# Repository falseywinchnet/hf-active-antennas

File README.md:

For the glory and the service of our God.

# HF active antennas

These are three open-hardware HF receive-antenna amplifiers. Each one ships with:
- an LTspice model you can simulate as delivered;
- a KiCad 10 board;
- JLCPCB-ready gerbers, BOM and pick-and-place;
- 3D renders and simulation plots.

All three use the Linear Systems **LSBF862** ultra-low-noise JFET at the input.

| | | |
|:---:|:---:|:---:|
|  |  |  |
| **[WB-2: zero-flux loop amplifier](wb2-loop-amplifier/)** | **[WB-LNA: loop preamplifier](wb-lna-loop-preamp/)** | **[MW-1: mini-whip E-field probe](mw1-mini-whip/)** |
| A balanced, transformer-feedback (zero-flux) amplifier for small receiving loops, Wellbrook ALA1530 class. 8 + 8 LSBF862, catalog Coilcraft transformers, 75 Ω F out. | A single-ended high-impedance preamp for a loop or any high-Z HF source. 4× LSBF862 common source → 4× NSVF4009 with shunt feedback, 50 Ω SMA. | A charge amplifier for a small capacitive plate (PA0RDT / PA3FWM class), built for linearity and spike survival. Jumper gain steps, 75 Ω F out, phantom power. |
| 0.1–30 MHz · 21.6 dB · NF 0.2–1.3 dB (50 Ω source) | 0.03–30 MHz · 24 dB · NF 0.8–1.1 dB | 9 kHz–30 MHz · OIP3 +47 dBm · OIP2 +73 dBm |
|  |  |  |

*Top row: KiCad 3D renders of the actual boards. Bottom row: AI-generated concept renders of the intended builds (ChatGPT image generation, from the KiCad renders and enclosure dimensions). They are not photographs; nothing has been built yet.*

## What is in each folder

| path | contents |
|---|---|
| `README.md` | the explanation, performance tables, plots and ordering notes |
| `images/` | 3D renders, copper plots, and the schematic as PNG and SVG |
| `ltspice/` | the `.asc` schematic plus every model library it needs. Open the `.asc` in LTspice and press Run; the `.lib` paths are relative. |
| `plots/` | simulation results |
| `jlcpcb/` | `*_gerbers_drill.zip` (upload this), the unzipped gerbers and drill files, `BOM_JLCPCB.csv` and `CPL_JLCPCB.csv` |
| `BOM.csv` | the full bill of materials, with manufacturer, MPN, footprint and status |
| `kicad/` | KiCad 10 board, project, custom footprint libraries and the DRC report |
| `*.step` | 3D board model for enclosure work |

## Status: read this before ordering
- **Simulation only.** Every performance figure here comes from LTspice. That includes nominal and tolerance corners, layout-parasitic models of the boards, and stability margins. **None of these boards has been built or measured yet.**
  - Treat the first boards as prototypes.
  - WB-2 has a first-board bring-up procedure in [`wb2-loop-amplifier/docs/BRINGUP.md`](wb2-loop-amplifier/docs/BRINGUP.md).
- **The LSBF862 is not stocked at LCSC.** Buy it from Linear Integrated Systems or a distributor, then hand-fit it or consign it to JLCPCB. The same applies to the Coilcraft transformers on WB-2.
- **No surge, ESD or lightning rating is claimed.** All three boards have protection networks, but none has been tested.
- **Check rotations in JLCPCB's placement preview.** KiCad and JLC disagree on the zero orientation of several packages (SOT-23, SOD-323, SC-82FL and others).
- **Model provenance:**
  - The LSBF862, NSVF4009 and MMBTH81 models are transcriptions of the manufacturers' published SPICE parameters, with LTspice syntax fixes noted in each file header.
  - The BC817-25 and 1N5819 come from LTspice's standard library.
  - The NSVF4015 model is a fit to its datasheet; onsemi publishes no model for it.
  - The protection parts, op-amps and the eFuse are behavioural.

## Tools
- [`tools/asc_render.py`](tools/asc_render.py) renders an LTspice `.asc` to PNG/SVG using LTspice's own symbol graphics. It needs LTspice installed for the `.asy` files. The schematic images were made with it.
- [`tools/net_compare.py`](tools/net_compare.py) compares an LTspice-generated `.net` against a reference SPICE netlist: element by element, value by value, with topology up to net renaming.
  - The WB-2 schematic is generated from the design's netlist and checked with it: 240 elements, 0 differences.
  - The AC response is identical to 1e-10 dB.

## License
Hardware design files, models and documentation are released under the **CERN Open Hardware Licence Version 2 – Permissive** ([`LICENSE`](LICENSE), SPDX `CERN-OHL-P-2.0`). They are provided as-is, without warranty; see sections 6–7 of the licence.

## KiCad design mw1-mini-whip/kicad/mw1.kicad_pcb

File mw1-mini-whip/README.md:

# MW-1: mini-whip E-field probe amplifier

*Concept render: AI-generated (ChatGPT image generation) from the KiCad renders and the enclosure dimensions, with a ruler for scale. It shows the intended build; it is **not** a photograph of a built unit.*

MW-1 is an active receiving antenna for 9 kHz – 30 MHz in the PA0RDT / PA3FWM / GigActiv class: a small capacitive plate on a mast, read by a low-noise amplifier.
- **Circuit:** a **charge amplifier** rather than the usual source follower. Gain is set by capacitance alone, so the gain steps are noiseless.
- **Design priorities:** linearity, overload margin and survival of nearby static and lightning spikes.
- **Plate:** 3 × 2 in (or a wire of similar size), about 10 pF.
- **Output and power:** 75 Ω F jack; +12 V phantom power up the coax.

## Performance
Simulated, coax-fed from a 12 V bias-T, so VCC at the board is 10.98 V at 103 mA. Field figures are referred to h_eff = 1 m.

| | 9 kHz | 100 kHz | 1 MHz | 7 MHz | 10 MHz | 30 MHz |
|---|---|---|---|---|---|---|
| Gain (V into 50 Ω per V/m) | −6.4 dB | −3.9 dB | −3.9 dB | −3.8 dB | −3.8 dB | −5.3 dB |
| Field noise (nV/m/√Hz) | | 30.5 | 4.5 | 3.4 | 3.4 | 3.8 |

- **OIP3** (7.0 / 7.1 MHz): **+47.3 dBm** at −3 dBm/tone; +44.3 dBm at +9 dBm/tone.
- **OIP2:** **+73.4 dBm**.
- **Output P1dB:** about +20 dBm.
- **FM band** (88–108 MHz): about −18 to −23 dB relative to 1 MHz.
- **Mains:** 50/60 Hz is about −110 dB.

**Installed height.** On a 3–4 m mast, h_eff is expected to be about 3.5 m. That lowers the field-referred noise about 3.5× (−11 dB), to roughly 1 nV/m/√Hz. That is 10–20 dB under quiet-rural plus galactic noise, so **overload margin, not sensitivity, is what the design spends its effort on.**

**Gain steps** (fit **at most one** jumper; output knee at h_eff 3.5 m, noise at 10 MHz with h_eff 1 m):

| jumper | added C_f | gain | output knee | noise floor |
|---|---|---|---|---|
| none | – | −3.9 dB | 1.5 V/m pk | 3.4 nV/m |
| JP1 | 33 pF | −13.6 dB | 4.5 V/m | 5.0 nV/m |
| JP2 | 130 pF | −23.6 dB | 14 V/m | 10.8 nV/m |
| JP3 | 470 pF | −33.5 dB | 44 V/m | 29 nV/m |

**Against published designs** (theirs measured or from datasheets, ours simulated):

| | OIP3 | OIP2 | field noise |
|---|---|---|---|
| **MW-1** | +47 dBm | +73 dBm | 3.4 nV/m/√Hz at h_eff 1 m |
| PA3FWM improved mini-whip | +40 to +43 | ≈ +70 | – |
| PA0RDT mini-whip | > +30 | > +50 | – |
| NTi GigActiv GA3005 | > +30 | > +50 | not published |
| R&S HE016 (6 m mast) | ≥ +30 | ≥ +50 | < 3.16 nV/m/√Hz |

## How it works

**Capacitive matching sets the floor.** The plate is a voltage source (E · h_eff) behind its own capacitance C_s. The field-referred noise floor is en · (C_s + C_stray + C_device) / (C_s · h_eff).
- **Every capacitance on the gate node counts.** That includes bootstrapped capacitance: a bootstrap's drive carries the device's own noise back through the same capacitor. This is Radeka's result for charge preamplifiers. It is why bootstrapping, the usual mini-whip trick, buys linearity but not noise.
- **Device choice:** with a 10 pF plate, the optimum device has C_dev ≈ C_s + stray. That points to the LSBF862.

**A charge amplifier instead of a follower:**
- **Input:** 2× LSBF862 in common source with an LSBF862 cascode, into an MMBTH81 current-source load.
- **Gain and output:** an NSVF4015 Darlington into two emitter followers, with NSVF4015 current sinks. The whole output stage is inside the loop.
- **Feedback:** C_f = 15 pF from OUT back to the gate, so the gate sits at virtual ground.
  - The JFET junctions barely move, which is where the +47 dBm OIP3 comes from.
  - Gain is C_s / C_f.
  - Raising C_f with a jumper raises headroom faster than it raises the noise floor. The steps are switched capacitance, so they add no noise.
- **Low-frequency and DC control:**
  - 1.5 MΩ + 100 nF in parallel with C_f roll off the low end and reject mains.
  - A BAV99 limiter in the feedback stops hard overload from latching the loop.
  - A TL431 / LM2904 bias and DC servo hold OUT at about 0.47 × VCC.

**Spike survival:** the protection is a staged chain.
- **Chain:**
  - a 90 V GDT and an SP4022 TVS at the plate;
  - a ±1.2 V BAV99 plate clamp, returned to its own decoupled node;
  - 100 Ω;
  - a ±0.6 V gate clamp.
- **Simulated with 20 V to 5 kV spikes** (ns edges) at the plate:
  - the output is pinned for ≤ 0.12 µs;
  - the in-band output is back under 10 mV in about 55 µs;
  - JFET gate conduction is ≤ 4.3 mA for about 1 ns.

**Power:** +12 V phantom only, through FB1 (600 Ω bead), then a 1 mH Würth WE-LQS choke, then 1 µF and an SMBJ15A, then a 100 µH / 47 µF filter, then 2.2 Ω, then VCC.
- **Feed drop:** about 1 V. A 13.8 V feed restores full headroom.
- **Bias-T:** not supplied. Use one rated ≥ 12 V / 150 mA with ≥ 1 kΩ choke impedance from 9 kHz to 30 MHz.

**Installation matters as much as the circuit.** The coax shield and mast are part of the antenna (PA3FWM). Ground the mast at its base and fit a common-mode choke on the coax there; Claessens measured a 15 dB difference.

## Plots

These curves come from the shipped `ltspice/mw1.asc`, not the design's Python reference model. The two agree within 0.5 dB.
- **Gain at 30 MHz:** −4.9 dB from the schematic, against the −5.3 dB in the table, which includes the layout estimate.
- **Field noise:** 4.5 / 3.3 / 3.4 / 3.7 nV/m at 1 / 7 / 10 / 30 MHz.

## LTspice model

`ltspice/mw1.asc` is the hand-laid schematic. Keep `lsbf862-ltspice.lib`, `mw-parts.lib`, `lna-parts.lib` and `mw1-nodeset.inc` next to it.
- **Test fixture:** VOC (AC 1 = 1 V/m at h_eff 1 m) behind the 10 pF plate capacitance, a 12 V shack bias-T, and a 50 Ω receiver. `V(rlo)` is the output.
- **Gain steps:** set `jp1`, `jp2` or `jp3 = 1` in the `.param` line.
- **Noise:** use `.noise V(rlo) VOC ...`, given on the sheet. `inoise` is then the field-referred noise in V/m/√Hz.
- **`mw1-nodeset.inc`:** a DC starting guess for the named nets. Without it, LTspice's operating-point search can stall with a jumper fitted. It does not change the solution.
- **Behavioural parts:** the op-amps, TL431 and GDT, as noted in `mw-parts.lib`.
- **NSVF4015 model:** a fit to its datasheet, since onsemi publishes no model for it.

## Board and ordering

**Board:**
- 92.4 × 42.4 mm, 2 layers, 1.6 mm FR-4, 1 oz copper, GND pours on both layers.
- **No copper pour within 1.5 mm of the plate/gate network on either layer.** This keeps stray capacitance off the node that sets the noise floor; the layout costs about 0.4 dB.
- **Enclosure:** Hammond 1591A (= RS PRO 153-3681, 100 × 50 × 25 mm) on 4 mm M3 standoffs.
- **Plate tab E1:** on the left edge. Slot that end wall for it, and mount the box plate-up with the coax down.
- **F jack J1:** on the right edge. Drill the wall for 3/8-32 with its axis about 13.45 mm above the inside floor. Fit a thin 3/8-32 jam nut (≤ 1.5 mm) or a 2 mm spacer inside as the stop.

**JLCPCB fabrication:** upload `jlcpcb/mw1_gerbers_drill.zip`.
- 2 layers, 1.6 mm, 1 oz;
- min track/clearance 0.2 mm, smallest via 0.6 / 0.3 mm;
- DRC: 0 violations, 0 unconnected.

**JLCPCB assembly:** `jlcpcb/BOM_JLCPCB.csv` and `jlcpcb/CPL_JLCPCB.csv`.
- **LCSC numbers:** filled only for J1. Let JLC match the rest by MPN or spec.
- **Hand-solder:** J1, JP1–JP3, and the plate. Solder the plate to both faces of E1.
- **Rotation:** check every part's rotation in the placement preview.
- **Cleaning:** the plate and gate network run at virtual ground through MΩ resistors. Wash the flux off, and consider conformal coating, but keep it off the plate tab.

**Measure on the prototype:**
- the JP3 step at 30 MHz (estimated 1–2.5 dB droop);
- the output-stage transistor temperatures;
- J1 return loss;
- the real h_eff and noise floor against a reference antenna.

## Files

| path | what |
|---|---|
| `ltspice/` | `mw1.asc`, its three model libraries, `mw1-nodeset.inc` |
| `images/` | concept render in the enclosure (AI-generated); 3D renders (iso, top, bottom); copper by net (both, top, bottom); the output end; placement with ratsnest; schematic (PNG, SVG) |
| `plots/` | gain steps and field-referred noise, from `ltspice/mw1.asc` |
| `jlcpcb/` | the gerber + drill zip, the unzipped files, `BOM_JLCPCB.csv`, `CPL_JLCPCB.csv` |
| `BOM.csv` | the full BOM: qty, designators, value, description, manufacturer, MPN, footprint, status |
| `kicad/` | `mw1.kicad_pcb`, the project, the custom footprint library `mw1.pretty`, the DRC report |
| `mw1.step` | 3D board model. The J1 body has no model. |

**Not claimed:** any surge/ESD rating or measured performance. All figures are simulation.

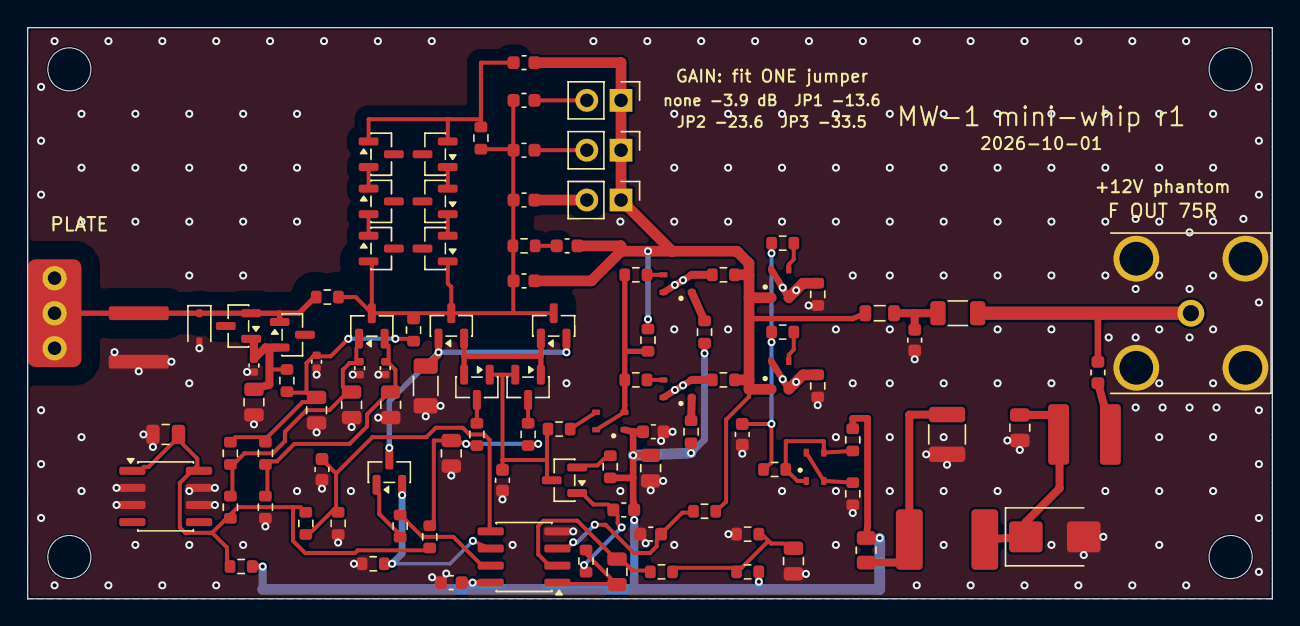
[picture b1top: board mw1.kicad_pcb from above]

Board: 2 copper layers, 92.4 x 42.4 mm, 109 parts (0 on the bottom side), 55 nets.

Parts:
C431: 10u; C_0805_2012Metric
CCOMP: 15p; C_0603_1608Metric
CDC: 100n; C_0603_1608Metric
CF: 15p; C_0603_1608Metric
CF2: 33p; C_0603_1608Metric
CF3: 130p; C_0603_1608Metric
CF4: 470p; C_0603_1608Metric
CFL: 47u; C_1210_3225Metric
CFM: 68p; C_0603_1608Metric
CIN: 1u; C_0805_2012Metric
CLIM: 470p; C_0603_1608Metric
CO: 22u; C_1206_3216Metric
CPB: 1u; C_0603_1608Metric
CPC1: 10u; C_0805_2012Metric
CPC2: 100n; C_0402_1005Metric
CRO: 10u; C_0805_2012Metric
CSB: 10u; C_1206_3216Metric
CSF: 1u; C_0603_1608Metric
CSI: 4.7u; C_0805_2012Metric
CSR: 1u; C_0603_1608Metric
CU1: 100n; C_0603_1608Metric
CVB: 10u; C_0805_2012Metric
CVC: 10u; C_0805_2012Metric
CVCLN1: 10u; C_0805_2012Metric
CVCLN2: 100n; C_0402_1005Metric
CVCLP1: 10u; C_0805_2012Metric
CVCLP2: 100n; C_0402_1005Metric
CVGREF1: 10u; C_0805_2012Metric
CVGREF2: 100n; C_0402_1005Metric
CVO: 100n; C_0603_1608Metric
CVS: 1u; C_0603_1608Metric
D1: SP4022; D_SOD-323
D2, D3, D4, D5, D6, D7, D8, D9, D10: DBAV99; SOT-23
D12: DTVS; D_SMB
E1: PLATE; PlateTab
FB1: 1.2u; L_0603_1608Metric
GDT1: GDT90; GDT25_S1
H1, H2, H3, H4: M3; MountingHole_3.2mm_M3
J1: F DOSIN-803-0182; F_DOSIN_803-0182_RA
JP1, JP2, JP3: JUMPER; PinHeader_1x02_P2.54mm_Vertical
LFD: 1m; WE-LQS_5040
LFL: 100u; L_2220_SIMID
LFM: 270n; L_0805_2012Metric
Q1, Q2, Q3, Q4: LSBF862_LTSPICE; SOT-23
Q5: BC817-25; SOT-23
Q6: MMBTH81; SOT-23
Q7, Q8, Q9, Q10, Q11, Q12: NSVF4015_FIT; SC-82FL_MCPH4
R1: 100; R_0603_1608Metric
R431: 2.2k; R_0603_1608Metric
RB: 2.2Meg; R_0603_1608Metric
RBF1, RBF2: 10; R_0603_1608Metric
RBP: 22; R_0603_1608Metric
RBS1, RBS2: 10; R_0603_1608Metric
RBSK: 470; R_0603_1608Metric
RCF1, RCF2: 2.2; R_0603_1608Metric
REF1, REF2: 1; R_0603_1608Metric
REL: 68; R_0603_1608Metric
RES1, RES2: 10; R_0603_1608Metric
RESK: 12; R_0603_1608Metric
RF: 1.5Meg; R_0603_1608Metric
RFL: 2.2; R_0805_2012Metric
RG3, RG4: 10; R_0603_1608Metric
RGRA: 14.0k; R_0603_1608Metric
RGRB: 1k; R_0603_1608Metric
RGRC: 1k; R_0603_1608Metric
RGRD: 9.09k; R_0603_1608Metric
RLB: 10Meg; R_0603_1608Metric
RMB: 10; R_0603_1608Metric
RMR: 1.69k; R_0603_1608Metric
RMRE: 100; R_0603_1608Metric
RPBD: 1k; R_0603_1608Metric
RPC: 100; R_0603_1608Metric
RPE: 1.5k; R_0603_1608Metric
RRO1: 10k; R_0603_1608Metric
RRO2: 9.1k; R_0603_1608Metric
RSF: 100k; R_0603_1608Metric
RSI: 10Meg; R_0603_1608Metric
RSR1: 9.1k; R_0603_1608Metric
RSR2: 1.0k; R_0603_1608Metric
RVB: 1k; R_0603_1608Metric
U1: LM2904; SOIC-8_3.9x4.9mm_P1.27mm
U2: TL431B; SOIC-8_3.9x4.9mm_P1.27mm

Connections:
CASC_S: Q1.2, Q2.1, Q3.2, Q4.1
D: CCOMP.1, Q3.1, Q4.2, Q6.3, RBP.2
FEED_B: FB1.2, LFD.1
FMO: CFM.1, CO.2, LFM.1
G: CF.2, CF2.2, CF3.2, CF4.2, D4.3, D7.2, D8.1, Q1.3, Q2.3, R1.1, RB.1, RF.2, RLB.2
GND: C431.2, CCOMP.2, CFL.2, CFM.2, CIN.2, CPC1.2, CPC2.2, CRO.2, CSB.2, CSF.2, CSR.2, CU1.2, CVB.2, CVC.2, CVCLN1.2, CVCLN2.2, CVCLP1.2, CVCLP2.2, CVGREF1.2, CVGREF2.2, CVO.2, CVS.2, D1.2, D12.2, GDT1.2, J1.2, RES1.2, RES2.2, RESK.2, RGRD.2, RMRE.2, RRO2.2, RSR2.2, U1.4, U2.2, U2.3, U2.6, U2.7
LIM: CLIM.2, D5.1, D10.2, RLB.1
MIR: Q12.1, Q12.3, RMB.1, RMR.2
OSF: CSF.1, RSF.2, U1.3
OUT: CDC.1, CF.1, CLIM.1, JP1.1, JP2.1, JP3.1, LFM.2, Q10.1, Q11.1, REF1.2, REF2.2, RPE.2, RSF.1
P003: CDC.2, RF.1
P004: CF2.1, JP1.2
P005: CF3.1, JP2.2
P006: CF4.1, JP3.2
P008: D5.2, D6.1
P010: D6.2, D7.1
P013: D8.2, D9.1
P015: D9.2, D10.1
PB: CPB.2, Q6.1, RPBD.1
PE: Q7.2, Q7.4, RBF1.2, RBF2.2, RPE.1
PLATE: D1.1, D2.1, D3.2, E1.1, GDT1.1, R1.2
Q3G: Q3.3, RG3.1
Q4G: Q4.3, RG4.1
Q6E: Q6.2, REL.2
Q7B: Q7.3, RBP.1
Q8B: Q8.3, RBF1.1
Q8C: Q8.1, RCF1.2
Q8E: Q8.2, Q8.4, REF1.1
Q9B: Q9.3, RBF2.1
Q9C: Q9.1, RCF2.2
Q9E: Q9.2, Q9.4, REF2.1
Q10B: Q10.3, RBS1.1
Q10E: Q10.2, Q10.4, RES1.1
Q11B: Q11.3, RBS2.1
Q11E: Q11.2, Q11.4, RES2.1
Q12E: Q12.2, Q12.4, RMRE.1
RFO: CO.1, FB1.1, J1.1
S: CSB.1, Q1.1, Q2.2, Q5.3
SINK_B: Q5.1, RBSK.1
SINK_E: Q5.2, RESK.1, U1.6
SM: CSI.2, RSI.1, U1.2
SVO: CSI.1, RPBD.2, U1.1
U1B_OUT: RBSK.2, U1.7
VB: CVB.1, RG3.2, RG4.2, RVB.2
VBS: CVS.1, RBS1.2, RBS2.2, RMB.2
VCC: CPB.1, CU1.1, CVC.1, CVO.1, Q7.1, R431.1, RCF1.1, RCF2.1, REL.1, RFL.1, RMR.1, RRO1.1, U1.8
VCLN: CVCLN1.1, CVCLN2.1, D4.2, RGRC.2, RGRD.1
VCLP: CVCLP1.1, CVCLP2.1, D4.1, RGRA.2, RGRB.1
VFEED: CIN.1, D12.1, LFD.2, LFL.2
VFL: CFL.1, LFL.1, RFL.2
VGREF: CVGREF1.1, CVGREF2.1, RB.2, RGRB.2, RGRC.1, RPC.2
VPC: CPC1.1, CPC2.1, D2.2, D3.1, RPC.1
VR25: C431.1, R431.2, RGRA.1, RSR1.1, RVB.1, U2.1, U2.8
VRO: CRO.1, RRO1.2, RRO2.1, RSI.2
VSR: CSR.1, RSR1.2, RSR2.1, U1.5

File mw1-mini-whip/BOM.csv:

Qty,Designators,Value,Description,Manufacturer,MPN,Footprint,Status
7,C431 CPC1 CRO CVB CVCLN1 CVCLP1 CVGREF1,10u 16V X7R,MLCC X7R 0805,,,C_0805_2012Metric,generic - any vendor to spec
2,CCOMP CF,15p 50V C0G,MLCC C0G/NP0 0603,,,C_0603_1608Metric,generic - any vendor to spec
3,CDC CU1 CVO,100n 25V X7R,MLCC X7R 0603,,,C_0603_1608Metric,generic - any vendor to spec
1,CF2,33p 50V C0G,MLCC C0G/NP0 0603,,,C_0603_1608Metric,generic - any vendor to spec
1,CF3,130p 50V C0G,MLCC C0G/NP0 0603,,,C_0603_1608Metric,generic - any vendor to spec
2,CF4 CLIM,470p 50V C0G,MLCC C0G/NP0 0603,,,C_0603_1608Metric,generic - any vendor to spec
1,CFL,47u 25V X5R,MLCC X5R 1210,,,C_1210_3225Metric,generic - any vendor to spec
1,CFM,68p 50V C0G,MLCC C0G/NP0 0603,,,C_0603_1608Metric,generic - any vendor to spec
1,CIN,1u 25V X7R,MLCC X7R 0805,,,C_0805_2012Metric,generic - any vendor to spec
1,CO,22u 25V X7R,MLCC X7R 1206,,,C_1206_3216Metric,generic - any vendor to spec
1,CPB,1u 25V X7R,MLCC X7R 0603,,,C_0603_1608Metric,generic - any vendor to spec
4,CPC2 CVCLN2 CVCLP2 CVGREF2,100n 16V X7R,MLCC X7R 0402,,,C_0402_1005Metric,generic - any vendor to spec
1,CSB,10u 16V X7R,MLCC X7R 1206,,,C_1206_3216Metric,generic - any vendor to spec
3,CSF CSR CVS,1u 16V X7R,MLCC X7R 0603,,,C_0603_1608Metric,generic - any vendor to spec
1,CSI,4.7u 25V X7R,MLCC X7R 0805,,,C_0805_2012Metric,generic - any vendor to spec
1,CVC,10u 25V X7R,MLCC X7R 0805,,,C_0805_2012Metric,generic - any vendor to spec
1,D1,SP4022,"TVS diode, bidirectional, 1.3 pF, SOD-323 (plate)",Littelfuse,SP4022-01FTG-C,D_SOD-323,verified against datasheet
9,D2 D3 D4 D5 D6 D7 D8 D9 D10,BAV99,"Dual series switching diode, trr 6 ns, SOT-23 (1=A1 2=K2 3=K1/A2)",onsemi,BAV99LT1G,SOT-23,verified against datasheet
1,D12,SMBJ15A,"TVS 15 V unidirectional, SMB (supply)",Littelfuse,SMBJ15A,D_SMB,generic - any vendor to spec
1,FB1,BLM18KG601,"Ferrite bead 600 ohm @100 MHz, 1.3 A, 0603 (phantom-feed hot end)",Murata,BLM18KG601SN1D,L_0603_1608Metric,verified against datasheet
1,GDT1,GDT25-09-S1,"Gas discharge tube 90 V, 2-electrode SMD (plate surge)",Bourns,GDT25-09-S1-RP,GDT25_S1,verified against datasheet
1,J1,F jack R/A,"F jack 75 ohm, right angle, PCB through hole, 3/8-32 + nut/washer, DC-3 GHz (LCSC C5119715)",Dosin,DOSIN-803-0182,F_DOSIN_803-0182_RA,verified against datasheet
3,JP1 JP2 JP3,JUMPER 2p,2-pin 2.54 mm header + shunt (gain step; fit at most one),,,PinHeader_1x02_P2.54mm_Vertical,generic - any vendor to spec
1,LFD,74404054102,"WE-LQS 5040 1 mH, 200 mA, 6 ohm, SRF 1.9 MHz, AEC-Q200 G1 (phantom-feed choke)",Wurth Elektronik,74404054102,WE-LQS_5040,verified against datasheet
1,LFL,B82442T1104K000,"SMD choke SIMID 2220-T 100 uH, 510 mA, 0.99 ohm (supply filter)",TDK,B82442T1104K000,L_2220_SIMID,verified against datasheet
1,LFM,0805CS-271XJL,"Ceramic-core wirewound 270 nH 5 %, 0805 (FM low-pass)",Coilcraft,0805CS-271XJL,L_0805_2012Metric,verified against datasheet
4,Q1 Q2 Q3 Q4,LSBF862,"N-channel JFET, ultra-low noise, SOT-23 (S/D interchangeable; 3=G)",Linear Integrated Systems,LSBF862,SOT-23,verified against datasheet
1,Q5,BC817-25,"NPN 45 V 500 mA, SOT-23 (JFET source sink)",onsemi,BC817-25LT1G,SOT-23,verified against datasheet
1,Q6,MMBTH81,"PNP RF 600 MHz, SOT-23 (D-node current-source load)",onsemi,MMBTH81LT1G,SOT-23,verified against datasheet
6,Q7 Q8 Q9 Q10 Q11 Q12,NSVF4015,"NPN RF 10 GHz 12 V 100 mA, SC-82FL/MCPH4 (1=C 2,4=E 3=B), AEC-Q101",onsemi,NSVF4015SG4T1G,SC-82FL_MCPH4,verified against datasheet
3,R1 RMRE RPC,100,Resistor 0603 1% thick film,,,R_0603_1608Metric,generic - any vendor to spec
1,R431,2.2k,Resistor 0603 1% thick film,,,R_0603_1608Metric,generic - any vendor to spec
1,RB,2.2M,Resistor 0603 1% thick film,,,R_0603_1608Metric,generic - any vendor to spec
9,RBF1 RBF2 RBS1 RBS2 RES1 RES2 RG3 RG4 RMB,10,Resistor 0603 1% thick film,,,R_0603_1608Metric,generic - any vendor to spec
1,RBP,22,Resistor 0603 1% thick film,,,R_0603_1608Metric,generic - any vendor to spec
1,RBSK,470,Resistor 0603 1% thick film,,,R_0603_1608Metric,generic - any vendor to spec
2,RCF1 RCF2,2.2,Resistor 0603 1% thick film,,,R_0603_1608Metric,generic - any vendor to spec
2,REF1 REF2,1,Resistor 0603 1% thick film,,,R_0603_1608Metric,generic - any vendor to spec
1,REL,68,Resistor 0603 1% thick film,,,R_0603_1608Metric,generic - any vendor to spec
1,RESK,12,Resistor 0603 1% thick film,,,R_0603_1608Metric,generic - any vendor to spec
1,RF,1.5M,Resistor 0603 1% thick film,,,R_0603_1608Metric,generic - any vendor to spec
1,RFL,2.2,Resistor 0805 1% thick film,,,R_0805_2012Metric,generic - any vendor to spec
1,RGRA,14.0k,Resistor 0603 1% thick film,,,R_0603_1608Metric,generic - any vendor to spec
2,RGRB RGRC,1k,Resistor 0603 0.1% thick film,,,R_0603_1608Metric,generic - any vendor to spec
1,RGRD,9.09k,Resistor 0603 1% thick film,,,R_0603_1608Metric,generic - any vendor to spec
2,RLB RSI,10M,Resistor 0603 1% thick film,,,R_0603_1608Metric,generic - any vendor to spec
1,RMR,1.69k,Resistor 0603 1% thick film,,,R_0603_1608Metric,generic - any vendor to spec
2,RPBD RVB,1k,Resistor 0603 1% thick film,,,R_0603_1608Metric,generic - any vendor to spec
1,RPE,1.5k,Resistor 0603 1% thick film,,,R_0603_1608Metric,generic - any vendor to spec
1,RRO1,10k,Resistor 0603 1% thick film,,,R_0603_1608Metric,generic - any vendor to spec
1,RRO2,9.1k,Resistor 0603 1% thick film,,,R_0603_1608Metric,generic - any vendor to spec
1,RSF,100k,Resistor 0603 1% thick film,,,R_0603_1608Metric,generic - any vendor to spec
1,RSR1,9.1k,Resistor 0603 0.1% thick film,,,R_0603_1608Metric,generic - any vendor to spec
1,RSR2,1.0k,Resistor 0603 0.1% thick film,,,R_0603_1608Metric,generic - any vendor to spec
1,U1,LM2904,"Dual op-amp, -40..125 C, SOIC-8 (A: DC servo, B: JFET sink)",onsemi,LM2904VDR2G,SOIC-8_3.9x4.9mm_P1.27mm,verified against datasheet
1,U2,TL431,"Shunt reference 2.495 V 0.4 %, -40..85 C, SOIC-8 (REF tied to K)",onsemi,TL431BIDR2G,SOIC-8_3.9x4.9mm_P1.27mm,verified against datasheet

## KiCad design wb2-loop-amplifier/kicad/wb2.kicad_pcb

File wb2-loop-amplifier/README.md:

# WB-2: zero-flux loop amplifier

*Concept render: AI-generated (ChatGPT image generation) from the KiCad renders and the enclosure dimensions, with a ruler for scale. It shows the intended build; it is **not** a photograph of a built unit.*

WB-2 is a balanced HF (0.1–30 MHz) amplifier for small receiving loops, in the Wellbrook ALA1530 class.
- **Feedback:** the loop is held near short circuit by lossless transformer feedback.
- **Parts:** catalog parts only, so there is no hand-wound transformer and no trimmer.
- **Power:** +12 V from either a DC jack or phantom feed up the coax.
- **Output:** 75 Ω F jack.

| | 1–7 MHz | 14 MHz | 21 MHz | 30 MHz |
|---|---|---|---|---|
| Gain (50 Ω source → 75 Ω load) | 21.6–21.8 dB | 21.1 dB | 19.0 dB | 15.8 dB |
| Noise figure (re 50 Ω) | 0.18–0.24 dB | 0.41 dB | 0.77 dB | 1.27 dB |

- **Linearity:** SFDR3 is 108–112.6 dB in 500 Hz.
- **Supply:** 75 mA at 12 V. The board operates from 11 to 15 V and switches itself off above about 17 V. It survives 24 V sustained.
- **Source:** these figures are simulation with nominal devices, using the layout-parasitic model of this board.

## How it works

**A small loop is an inductive source.** Its EMF rises with frequency, and so does its reactance, so the **short-circuit current** is flat with frequency. The Wellbrook idea is to amplify that current while holding the loop terminals near zero volts. The loop then carries almost no net signal flux, which gives the topology its "zero-flux" name.

**The hold is done with transformer feedback, not resistors.** Transformers add no thermal noise, so the feedback costs essentially nothing in noise figure.
- **T1 (Coilcraft WB16-6T)** senses the loop voltage. Its centre-tapped secondary drives the two gate buses, GA and GB.
- **The input stage** is two banks of 4× LSBF862 in common source, one bank per half.
- **T3/T4 (2× WB36-1)** carry the feedback. Each half's source current flows through the 25 µH winding of one of them; the 900 µH winding sits across the loop, a 6:1 turns ratio. It is phased so the returned current opposes the loop voltage.
- **Result:** with high loop gain, the loop sees a near-short, and the drain current is a faithful copy of the loop's short-circuit current.

**Bias:** each half runs at 33.8 mA.
- An op-amp current sink sets it, replacing the original's verostat. LM358B and BC817-25 force V(E) = 0.50 V across 14.7 Ω.
- The sink sits behind a 1 mH choke, so its noise never reaches the summing node.
- A TL431 sets all the bias references, so the currents don't depend on the supply.
- The gate buses sit at 1.50 V through T1's centre tap. They are clamped by antiparallel BAV99s that see zero DC, so they add no leakage noise.

**Cascode and output:**
- **Cascode:** 2× 4 LSBF862 in common gate, with 10 Ω gate stoppers. The gates sit at VBB = 5.0 V, locally bypassed. A JFET cascode has no base current, so there is no partition noise.
- **Output:** push-pull into T2 (WB5-1T), with the centre tap fed from VDD. C16 blocks DC from the coax, because the coax may carry phantom power.

**Stability at VHF.** The worst stability case is a VHF mode at 43–52 MHz through T1's leakage inductance. It shows up with multi-turn or high-inductance loops, for example 14.5 µH with 40 nH leads.
- **Snubber:** R3 + C1 across the loop pins sets the margin.
- **C1 = 15 pF (baseline):** 4° phase margin on such a loop.
- **C1 = 33 pF (option):** 36° phase margin.
- **Choosing:** fit 15 pF for 1 m-class single-turn loops and 33 pF for big or multi-turn loops. `plots/2_vhf_loopgain.png` shows the Middlebrook loop gain at the C3/C4 pads.

**Power entry:** two feeds, diode-ORed, then a shared protection chain.
- **Feeds:** the DC jack through a Würth 744222 common-mode choke, or +12 V phantom up the coax through L6‖R27, a 1 mH choke and a bead.
- **Protection chain:**
  - a 200 mA PTC;
  - an SMBJ26A TVS;
  - a TPS26621 eFuse as an over-voltage cut-off (17.16 V rising, 16.0 V falling);
  - a PMEG4020 output clamp;
  - a 100 µH / 1 µF LC, then 4.7 Ω / 220 µF.

## Plots

## LTspice model

`ltspice/wb2.asc` is the complete simulation model: 240 elements, every board part plus the layout lead inductances.
- **Supporting files:** `sp4022.asy` (TVS symbol), `lsbf862-ltspice.lib` and `wb2-parts.lib`. Keep them next to the `.asc`.
- **How it was made:** the schematic is generated from the design's own netlist, and LTspice's netlist of it was checked against that netlist element by element (`../tools/net_compare.py`). The simulated response is identical.
- **Coupled windings** are LTspice `ind2` inductors (the dot is the first node) with K statements at k = 0.9995.
- **Default analysis:** `.ac` with a 50 Ω generator (VSIG, RS) across the loop posts into a 75 Ω receiver.
  - `V(out)` is the load voltage.
  - Transducer gain is `20·log|V(out)| + 10·log(200/75)` dB.
- **Noise:** swap the `.ac` for `.noise V(out) VSIG dec 30 10k 60Meg`. `inoise` is then referred to the 50 Ω source.
- **Loop gain:** VBRA/VBRB are 0 V break points. Make them AC sources for Middlebrook V/I injection.
- **Behavioural blocks** (stated on the sheet): the op-amp, the TL431 and the eFuse.

## Board and ordering

**Board:**
- 96 × 76 mm, 2 layers, 1.6 mm FR-4, 1 oz copper, solid GND pours on both layers.
- **Enclosure:** Hammond **1554F2GY** (IP66). The board mounts on the box's M3 inserts (77 × 68 mm) on 10 mm standoffs; the corner bites clear the lid-screw columns.
- **Connectors:** all panel-mounted and wired to the board.
  - Left wall: loop posts J1/J2 and the ground post J3.
  - Right wall: F jack J4 (RG-179 pigtail ≤ 50 mm) and DC jack J5.
- **Mechanical drawing:** `docs/wb2_mechanical.pdf` (rev C) gives the wall-hole positions, checked against the connector makers' drawings. It is not a drilling template until the box datums are measured.
  - **Left wall:** Cliff CL1505 posts (13.3 mm collars, 7 mm keyed holes) at 19.05 mm pitch, so a dual 4 mm plug fits LOOP A/B.
  - **Right wall:** the 222114-10 F jack mounts from the rear (12.9 mm flange inside). The 721AU's 14.3 mm body sits inside the wall, clear of the lid-screw column.
  - **721AU nut:** its bushing is only 4.6 mm long, so check nut engagement on the 3 mm wall and counterbore from inside if it is short.

**JLCPCB fabrication:** upload `jlcpcb/wb2_gerbers_drill.zip`.
- 2 layers, 96 × 76 mm, 1.6 mm, 1 oz;
- min track/space 0.2 mm, min drill 0.2 mm (the U3 thermal vias);
- HASL-LF or ENIG.

**JLCPCB assembly** (top side, optional): upload `jlcpcb/BOM_JLCPCB.csv` and `jlcpcb/CPL_JLCPCB.csv`.
- **Contents:** 115 SMD parts. The CPL uses the gerbers' absolute origin, in mm.
- **LCSC numbers:** the column is left empty. Match parts in JLC's BOM tool by manufacturer/MPN. Generic passives can be any vendor to the stated dielectric and voltage.
- **Rotation:** check every part's rotation in the placement preview. This matters most for SOT-23, VSON-10, SOD-123F and the Coilcraft WB parts. Pin 1 of the WB transformers is the dot.
- **Supply your own:** the LSBF862s, Vgs-matched within each bank, and probably the Coilcraft transformers.

**Hand assembly:**
- C19 is a 220 µF radial (THT). Mind the polarity.
- The panel wiring and the RG-179 pigtail, laced at its two holes.
- D12/D13 are DNP evaluation pads.

## Files

| path | what |
|---|---|
| `ltspice/` | `wb2.asc`, `sp4022.asy`, `lsbf862-ltspice.lib`, `wb2-parts.lib` |
| `images/` | concept render in the enclosure (AI-generated); 3D renders (iso, top, bottom); copper coloured by net (top, bottom); test-pad map; mechanical drawing; schematic (PNG, SVG) |
| `plots/` | gain/NF (hard-pass model vs board copper); VHF loop gain with C1 15 vs 33 pF |
| `jlcpcb/` | the gerber + drill zip, the unzipped files (Excellon in mm, PTH and NPTH separate, with maps), `BOM_JLCPCB.csv`, `CPL_JLCPCB.csv` |
| `BOM.csv` | the full BOM: designators, value, description, manufacturer, MPN, footprint, status (specified / generic / THT / panel / DNP / mechanical) |
| `kicad/` | `wb2.kicad_pcb`, the project, footprint libraries (`wb2.pretty`, `wblna.pretty`), the custom 3D bodies (`wb2.3dshapes`), netlist and footprint tables, DRC report (0 unconnected, 0 clearance) |
| `docs/BRINGUP.md` | first-board bring-up procedure: power-up, bias, the transformer-phasing check, the stability matrix for the C1 decision |
| `docs/SOURCING.md` | lifecycle and sourcing table |
| `docs/README-LAYOUT.md` | the floorplan and the reasoning behind the placement |
| `docs/testpoints.md`, `docs/*.pdf` | test-pad map; assembly, copper and mechanical drawings |
| `wb2.step` | 3D board model. The Coilcraft and pigtail bodies are simple boxes. |

The docs mention numbered design reviews (review-06, -08 and so on). Those were internal review rounds of the schematic and layout; their conditions are folded into these documents.

**Not claimed:** any surge/ESD rating, measured RF performance or thermal qualification. All figures are simulation.

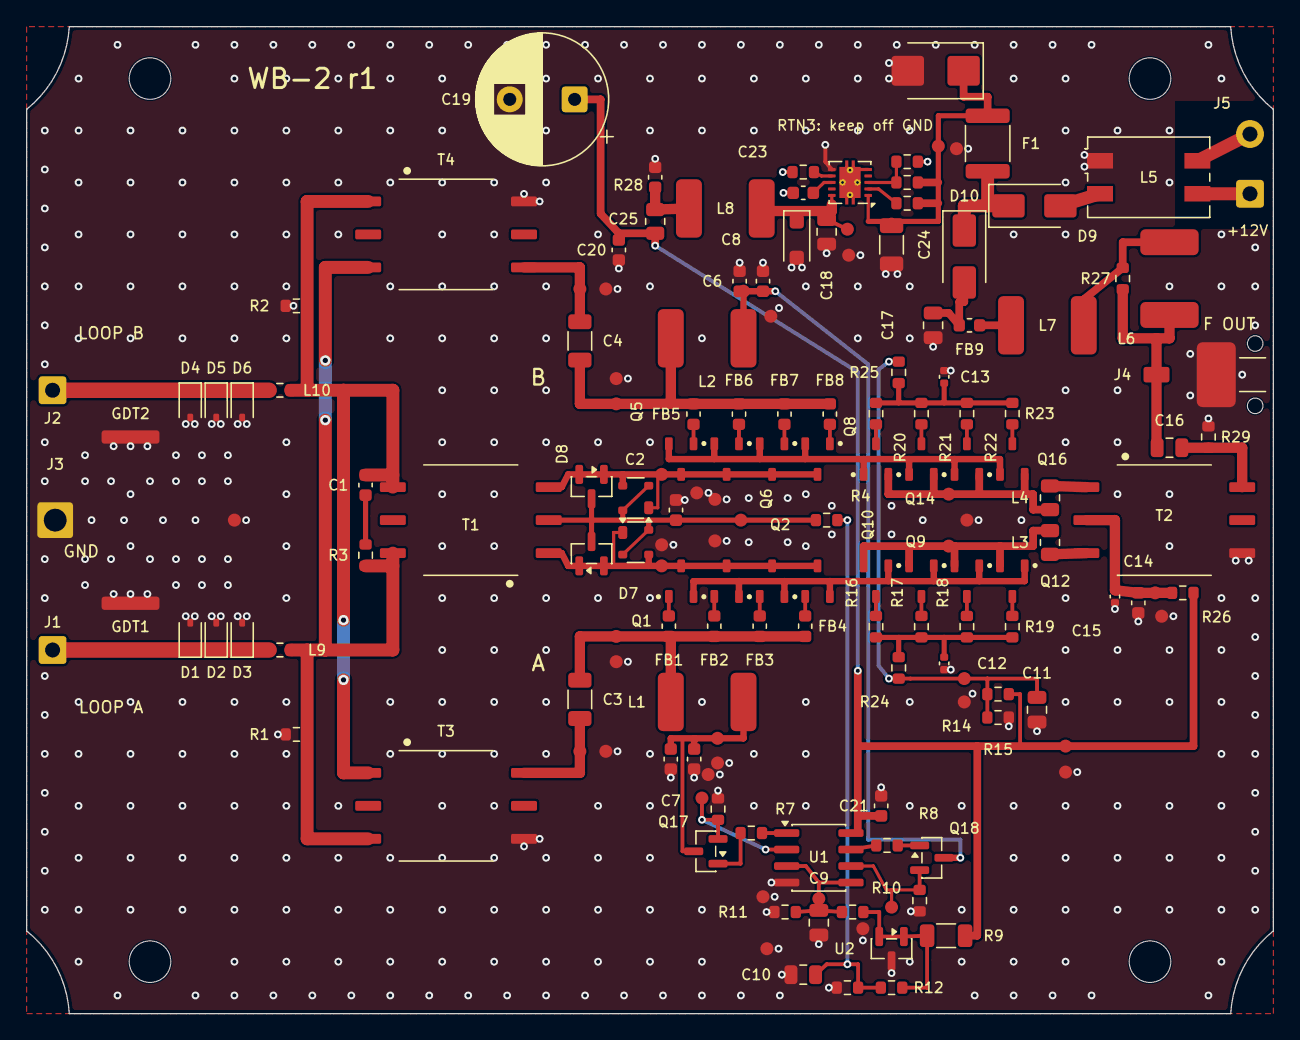
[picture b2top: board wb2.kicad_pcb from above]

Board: 2 copper layers, 96.0 x 76.0 mm, 167 parts (0 on the bottom side), 68 nets.

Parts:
C1: 15p; C_0603_1608Metric
C2, C21: 100n; C_0603_1608Metric
C3, C4: 10u; C_1206_3216Metric
C5, C6, C14, C20, C25: 1u; C_0603_1608Metric
C7, C8: 10n; C_0603_1608Metric
C9, C10, C11: 10u; C_0805_2012Metric
C12, C13, C15: 10n; C_0402_1005Metric
C16, C17, C18: 1u; C_0805_2012Metric
C19: 220u; CP_Radial_D10.0mm_P5.00mm
C23: 220n; C_0603_1608Metric
C24: 2.2u; C_1206_3216Metric
D1, D2, D3, D4, D5, D6: SP4022; D_SOD-323
D7, D8: BAV99; SOT-23
D9, D10: SS14; D_SMA
D11: SMBJ26A; D_SMB
D12, D13: BAV23 (DNP); SOT-143
D14: PMEG4020ER; D_SOD-123F
F1: PTC 200 mA hold 60 V; Fuse_1812_4532Metric
FB1, FB2, FB3, FB4, FB5, FB6, FB7, FB8: 470R@100M; L_0603_1608Metric
FB9: 600R@100M; L_0603_1608Metric
GDT1, GDT2: 90 V; GDT25_S1
H1, H2, H3, H4: M3; MountingHole_3.2mm_M3
J1: LOOP A; SolderWire-0.5sqmm_1x01_D0.9mm_OD2.1mm
J2: LOOP B; SolderWire-0.5sqmm_1x01_D0.9mm_OD2.1mm
J3: GND; SolderWire-1sqmm_1x01_D1.4mm_OD2.7mm
J4: F-female; F_Pigtail_2pad
J5: 12 V jack; SolderWire-0.5sqmm_1x02_P4.6mm_D0.9mm_OD2.1mm
L1, L2, L7: 1m; L_2220_SIMID
L3, L4: 0R link; R_0805_2012Metric
L5: 744222; L_CommonMode_Wuerth_WE-SL2
L6, L8: 100u; L_2220_SIMID
L9, L10: 0R link; R_0603_1608Metric
Q1, Q2, Q3, Q4, Q5, Q6, Q7, Q8, Q9, Q10, Q11, Q12, Q13, Q14, Q15, Q16: LSBF862; SOT-23_WB
Q17, Q18: BC817-25; SOT-23
R1, R2: 100k; R_0603_1608Metric
R3: 150; R_0603_1608Metric
R4, R24, R25: 100; R_0603_1608Metric
R5, R6: 14.7; R_0603_1608Metric
R7, R8: 470; R_0603_1608Metric
R9: 1.5k; R_1206_3216Metric
R10: 2.0k; R_0603_1608Metric
R11: 499; R_0603_1608Metric
R12: 1.0k; R_0603_1608Metric
R13: 1.5k; R_0603_1608Metric
R14, R35: 10k; R_0603_1608Metric
R15: 8.2k; R_0603_1608Metric
R16, R17, R18, R19, R20, R21, R22, R23: 10; R_0603_1608Metric
R26: 1; R_0603_1608Metric
R27: 1k; R_0603_1608Metric
R28: 4.7; R_0805_2012Metric
R29: 2.2k; R_0603_1608Metric
R33: 1.02M; R_0603_1608Metric
R34: 133k; R_0603_1608Metric
R36: 26.7k; R_0603_1608Metric
T1: WB16-6T; Coilcraft_WB_SMD
T2: WB5-1T; Coilcraft_WB_SMD
T3, T4: WB36-1; Coilcraft_WB_SMD
TP1: GA; TP_Pad_1.0mm
TP2: GB; TP_Pad_1.0mm
TP3: GCT; TP_Pad_1.0mm
TP4: SA; TP_Pad_1.0mm
TP5: SB; TP_Pad_1.0mm
TP6: SAK; TP_Pad_1.0mm
TP7: SBK; TP_Pad_1.0mm
TP8: XA; TP_Pad_1.0mm
TP9: XB; TP_Pad_1.0mm
TP10: ESA; TP_Pad_1.0mm
TP11: ESB; TP_Pad_1.0mm
TP12: CA; TP_Pad_1.0mm
TP13: CB; TP_Pad_1.0mm
TP14: REF; TP_Pad_1.0mm
TP15: VBB; TP_Pad_1.0mm
TP16: T2CT; TP_Pad_1.0mm
TP17: VDD; TP_Pad_1.0mm
TP18: vp; TP_Pad_1.0mm
TP19: vpo; TP_Pad_1.0mm
TPG1, TPG2, TPG3, TPG4, TPG5, TPG6, TPG7, TPG8, TPG9, TPG10, TPG11, TPG12, TPG13, TPG14, TPG15, TPG16, TPG17, TPG18, TPG19, TPG20, TPG21: GND; TP_Pad_1.0mm
U1: LM358B; SOIC-8_3.9x4.9mm_P1.27mm
U2: TL431; SOT-23
U3: TPS26621; Texas_DRC0010J_ThermalVias

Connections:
BA: C12.1, R16.2, R17.2, R18.2, R19.2, R24.1
BB: C13.1, R20.2, R21.2, R22.2, R23.2, R25.1
BSA: Q17.1, R7.2
BSB: Q18.1, R8.2
CA: L3.1, Q9.2, Q10.2, Q11.2, Q12.2, TP12.1
CAt: L3.2, T2.3
CB: L4.1, Q13.2, Q14.2, Q15.2, Q16.2, TP13.1
CBL_GND: J5.2, L5.4
CBt: L4.2, T2.1
DA: Q1.2, Q2.2, Q3.2, Q4.2, Q9.1, Q10.1, Q11.1, Q12.1
DB: Q5.2, Q6.2, Q7.2, Q8.2, Q13.1, Q14.1, Q15.1, Q16.1
DV3: C23.1, U3.8
ESA: Q17.2, R5.1, TP10.1, U1.2
ESB: Q18.2, R6.1, TP11.1, U1.6
GA: D7.1, D7.2, D12.1, D12.3, Q1.3, Q2.3, Q3.3, Q4.3, T1.1, TP1.1
GB: D8.1, D8.2, D13.1, D13.3, Q5.3, Q6.3, Q7.3, Q8.3, T1.3, TP2.1
GBIAS: C10.1, R4.1, R12.2, R13.1
GCA0: Q9.3, R16.1
GCA1: Q10.3, R17.1
GCA2: Q11.3, R18.1
GCA3: Q12.3, R19.1
GCB0: Q13.3, R20.1
GCB1: Q14.3, R21.1
GCB2: Q15.3, R22.1
GCB3: Q16.3, R23.1
GCT: C2.1, D7.3, D8.3, D12.2, D12.4, D13.2, D13.4, R4.2, T1.2, TP3.1
GND: C2.2, C5.2, C6.2, C7.2, C8.2, C9.2, C10.2, C11.2, C12.2, C13.2, C14.2, C15.2, C17.2, C18.2, C19.2, C20.2, C21.2, C24.2, C25.2, D1.2, D2.2, D3.2, D4.2, D5.2, D6.2, D11.2, D14.2, GDT1.2, GDT2.2, J3.1, J4.2, L5.1, R1.2, R2.2, R5.2, R6.2, R11.2, R13.2, R15.2, R29.2, T2.4, T3.4, T4.6, TPG1.1, TPG2.1, TPG3.1, TPG4.1, TPG5.1, TPG6.1, TPG7.1, TPG8.1, TPG9.1, TPG10.1, TPG11.1, TPG12.1, TPG13.1, TPG14.1, TPG15.1, TPG16.1, TPG17.1, TPG18.1, TPG19.1, TPG20.1, TPG21.1, U1.4, U2.3, U3.6
IL3: R36.1, U3.7
LA: L9.2, R1.1, R3.1, T1.6, T3.3, T4.3
LAP: D1.1, D2.1, D3.1, GDT1.1, J1.1, L9.1
LB: C1.2, L10.2, R2.1, T1.4, T3.1, T4.1
LBP: D4.1, D5.1, D6.1, GDT2.1, J2.1, L10.1
OOA: R7.1, U1.1
OOB: R8.1, U1.7
OUTH: C16.1, R29.1, T2.6
OV3: R34.2, R35.1, U3.3
REF: C9.1, R10.2, R11.1, TP14.1, U1.3, U1.5
RFO: C16.2, J4.1, L6.1, R27.1
RTN3: C23.2, R35.2, R36.2, U3.5, U3.11
SA: C3.1, FB1.2, FB2.2, FB3.2, FB4.2, L1.1, TP4.1
SAK: C3.2, T3.6, TP6.1
SB: C4.1, FB5.2, FB6.2, FB7.2, FB8.2, L2.1, TP5.1
SBK: C4.2, T4.4, TP7.1
T2CT: C14.1, C15.1, R26.2, T2.2, TP16.1
UV3: R33.2, U3.2
V25: R9.2, R10.1, R12.1, U2.1, U2.2
VBB: C11.1, R14.2, R15.1, R24.2, R25.2, TP15.1
VDD: C19.1, C20.1, C21.1, R9.1, R14.1, R26.1, R28.2, TP17.1, U1.8
XA: C5.1, C7.1, L1.2, Q17.3, TP8.1
XB: C6.1, C8.1, L2.2, Q18.3, TP9.1
l6c: L6.2, L7.1, R27.2
sA0: FB1.1, Q1.1
sA1: FB2.1, Q2.1
sA2: FB3.1, Q3.1
sA3: FB4.1, Q4.1
sB0: FB5.1, Q5.1
sB1: FB6.1, Q6.1
sB2: FB7.1, Q7.1
sB3: FB8.1, Q8.1
snA: C1.1, R3.2
vcf: C17.1, D10.2, FB9.2
vcfb: FB9.1, L7.2
vin: J5.1, L5.3
vj: D9.2, L5.2
vor: D9.1, D10.1, F1.1
vp: C24.1, D11.1, F1.2, R33.1, R34.1, TP18.1, U3.1
vpo: C18.1, D14.1, L8.1, TP19.1, U3.10
vq: C25.1, L8.2, R28.1

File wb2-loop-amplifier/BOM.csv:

Qty,Designators,Value,Description,Manufacturer,MPN,Footprint,Status
1,C1,15p,0603 C0G 50 V,,,C_0603_1608Metric,generic (any vendor to spec)
2,C2 C21,100n,0603 X7R 25 V,,,C_0603_1608Metric,generic (any vendor to spec)
2,C3 C4,10u,1206 X7R 16 V,,,C_1206_3216Metric,generic (any vendor to spec)
2,C5 C6,1u,0603 X7R 16 V,,,C_0603_1608Metric,generic (any vendor to spec)
2,C7 C8,10n,0603 X7R 25 V,,,C_0603_1608Metric,generic (any vendor to spec)
3,C9 C10 C11,10u,0805 X7R 16 V,,,C_0805_2012Metric,generic (any vendor to spec)
2,C12 C13,10n,0402 X7R 16 V,,,C_0402_1005Metric,generic (any vendor to spec)
3,C14 C20 C25,1u,0603 X7R 25 V,,,C_0603_1608Metric,generic (any vendor to spec)
1,C15,10n,0402 X7R 25 V,,,C_0402_1005Metric,generic (any vendor to spec)
3,C16 C17 C18,1u,0805 X7R 50 V,,,C_0805_2012Metric,generic (any vendor to spec)
1,C19,220u,"EEU-FC1V221B, 220 uF 35 V 105 C, 10 x 12.5 mm, 5 mm pitch (review-06 freeze; confirm active at order)",Panasonic,EEU-FC1V221B,CP_Radial_D10.0mm_P5.00mm,THT (hand assembly)
1,C23,220n,0603 X7R 25 V,,,C_0603_1608Metric,generic (any vendor to spec)
1,C24,2.2u,1206 X7R 50 V,,,C_1206_3216Metric,generic (any vendor to spec)
6,D1 D2 D3 D4 D5 D6,SP4022,SP4022-01FTG-C,Littelfuse,SP4022-01FTG-C,D_SOD-323,specified
2,D7 D8,BAV99,BAV99LT1G (active; sourcing rule: no NXP-lineage parts),onsemi,BAV99LT1G,SOT-23,specified
2,D9 D10,SS14,SS14,onsemi,SS14,D_SMA,specified
1,D11,SMBJ26A,SMBJ26A,Littelfuse,SMBJ26A,D_SMB,specified
0,D12 D13,BAV23 (DNP),BAV23 (evaluation footprint),Nexperia,BAV23,SOT-143,DNP
1,D14,PMEG4020ER,"PMEG4020ER (40 V 2 A Schottky, 50 A surge)",Nexperia,PMEG4020ER,D_SOD-123F,specified
1,F1,PTC 200 mA hold 60 V,MF-MSMF020/60-2,Bourns,MF-MSMF020/60-2,Fuse_1812_4532Metric,specified
8,FB1 FB2 FB3 FB4 FB5 FB6 FB7 FB8,470R@100M,BLM18PG471SN1D,Murata,BLM18PG471SN1D,L_0603_1608Metric,specified
1,FB9,600R@100M,BLM18KG601SN1D,Murata,BLM18KG601SN1D,L_0603_1608Metric,specified
2,GDT1 GDT2,90 V,GDT25-09-S1-RP,Bourns,GDT25-09-S1-RP,GDT25_S1,specified
1,J1,LOOP A,CL1505 4 mm binding post,Cliff,CL1505,SolderWire-0.5sqmm_1x01_D0.9mm_OD2.1mm,panel / wired (hand assembly)
1,J2,LOOP B,CL1505 4 mm binding post,Cliff,CL1505,SolderWire-0.5sqmm_1x01_D0.9mm_OD2.1mm,panel / wired (hand assembly)
1,J3,GND,CL1505 4 mm binding post,Cliff,CL1505,SolderWire-1sqmm_1x01_D1.4mm_OD2.7mm,panel / wired (hand assembly)
1,J4,F-female,"222114-10 rear-bulkhead F jack, 75 ohm, RG-179 crimp (use the prescribed assembly); <= 50 mm RG-179 pigtail to the board pads",Amphenol RF,222114-10,F_Pigtail_2pad,panel / wired (hand assembly)
1,J5,12 V jack,"721AU panel-mount 2.1 mm DC jack, IP68, solder terminals; short twisted pair to the board",Switchcraft,721AU,SolderWire-0.5sqmm_1x02_P4.6mm_D0.9mm_OD2.1mm,panel / wired (hand assembly)
3,L1 L2 L7,1m,B82442T1105K000,TDK,B82442T1105K000,L_2220_SIMID,specified
2,L3 L4,0R link,WFZ0805 low-resistance jumper (peaking position; no inductor),Vishay,WFZ0805,R_0805_2012Metric,specified
1,L5,744222,744222,Wurth,744222,L_CommonMode_Wuerth_WE-SL2,specified
2,L6 L8,100u,B82442T1104K000,TDK,B82442T1104K000,L_2220_SIMID,specified
2,L9 L10,0R link,WFZ0603 low-resistance jumper (verify R; footprint reserved for a series L),Vishay,WFZ0603,R_0603_1608Metric,specified
8,Q1 Q2 Q3 Q4 Q5 Q6 Q7 Q8,LSBF862,"LSBF862 (SOT-23), Vgs-selected at 8.5 mA",Linear Systems,LSBF862,SOT-23_WB,specified
8,Q9 Q10 Q11 Q12 Q13 Q14 Q15 Q16,LSBF862,"LSBF862 (SOT-23), same selection as Q1-Q8 or higher Idss",Linear Systems,LSBF862,SOT-23_WB,specified
2,Q17 Q18,BC817-25,BC817-25LT1G (active; sourcing rule: no NXP transistors),onsemi,BC817-25LT1G,SOT-23,specified
2,R1 R2,100k,0603 1%,,,R_0603_1608Metric,generic (any vendor to spec)
1,R3,150,0603 1%,,,R_0603_1608Metric,generic (any vendor to spec)
3,R4 R24 R25,100,0603 1%,,,R_0603_1608Metric,generic (any vendor to spec)
2,R5 R6,14.7,0603 0.1% (Kelvin-routed),,,R_0603_1608Metric,generic (any vendor to spec)
2,R7 R8,470,0603 1%,,,R_0603_1608Metric,generic (any vendor to spec)
1,R9,1.5k,1206 1% 0.25 W,,,R_1206_3216Metric,generic (any vendor to spec)
1,R10,2.0k,0603 0.1%,,,R_0603_1608Metric,generic (any vendor to spec)
1,R11,499,0603 0.1%,,,R_0603_1608Metric,generic (any vendor to spec)
1,R12,1.0k,0603 1%,,,R_0603_1608Metric,generic (any vendor to spec)
1,R13,1.5k,0603 1%,,,R_0603_1608Metric,generic (any vendor to spec)
2,R14 R35,10k,0603 1%,,,R_0603_1608Metric,generic (any vendor to spec)
1,R15,8.2k,0603 1%,,,R_0603_1608Metric,generic (any vendor to spec)
8,R16 R17 R18 R19 R20 R21 R22 R23,10,0603 1%,,,R_0603_1608Metric,generic (any vendor to spec)
1,R26,1,0603,,,R_0603_1608Metric,generic (any vendor to spec)
1,R27,1k,0603 1%,,,R_0603_1608Metric,generic (any vendor to spec)
1,R28,4.7,0805 1%,,,R_0805_2012Metric,generic (any vendor to spec)
1,R29,2.2k,0603 1%,,,R_0603_1608Metric,generic (any vendor to spec)
1,R33,1.02M,0603 1%,,,R_0603_1608Metric,generic (any vendor to spec)
1,R34,133k,0603 1%,,,R_0603_1608Metric,generic (any vendor to spec)
1,R36,26.7k,0603 1%,,,R_0603_1608Metric,generic (any vendor to spec)
1,T1,WB16-6T,WB16-6TSLD (SMD; TH equivalent WB16-6TL),Coilcraft,WB16-6TSLD,Coilcraft_WB_SMD,specified
1,T2,WB5-1T,WB5-1TSLD (SMD; TH equivalent WB5-1TL),Coilcraft,WB5-1TSLD,Coilcraft_WB_SMD,specified
2,T3 T4,WB36-1,WB36-1SLD (SMD; TH equivalent WB36-1L),Coilcraft,WB36-1SLD,Coilcraft_WB_SMD,specified
1,U1,LM358B,LM358BIDR (SOIC-8),TI,LM358BIDR,SOIC-8_3.9x4.9mm_P1.27mm,specified
1,U2,TL431,TL431BIDBZR,TI,TL431BIDBZR,SOT-23,specified
1,U3,TPS26621,TPS26621DRCR (VSON-10),TI,TPS26621DRCR,Texas_DRC0010J_ThermalVias,specified
1,(enclosure),1554F2GY,"Polycarbonate IP66 box 120 x 90 x 61 mm, PCB on the M3 brass inserts",Hammond,1554F2GY,-,mechanical
4,(H1-H4),M3 x 10,M3 F-F hex standoff 10 mm + 8x M3 x 6 screws,,,-,mechanical
1,(J4 cable),RG-179,"<= 50 mm RG-179 pigtail, 222114-10 crimp end, soldered to the J4 landing",,,-,mechanical
